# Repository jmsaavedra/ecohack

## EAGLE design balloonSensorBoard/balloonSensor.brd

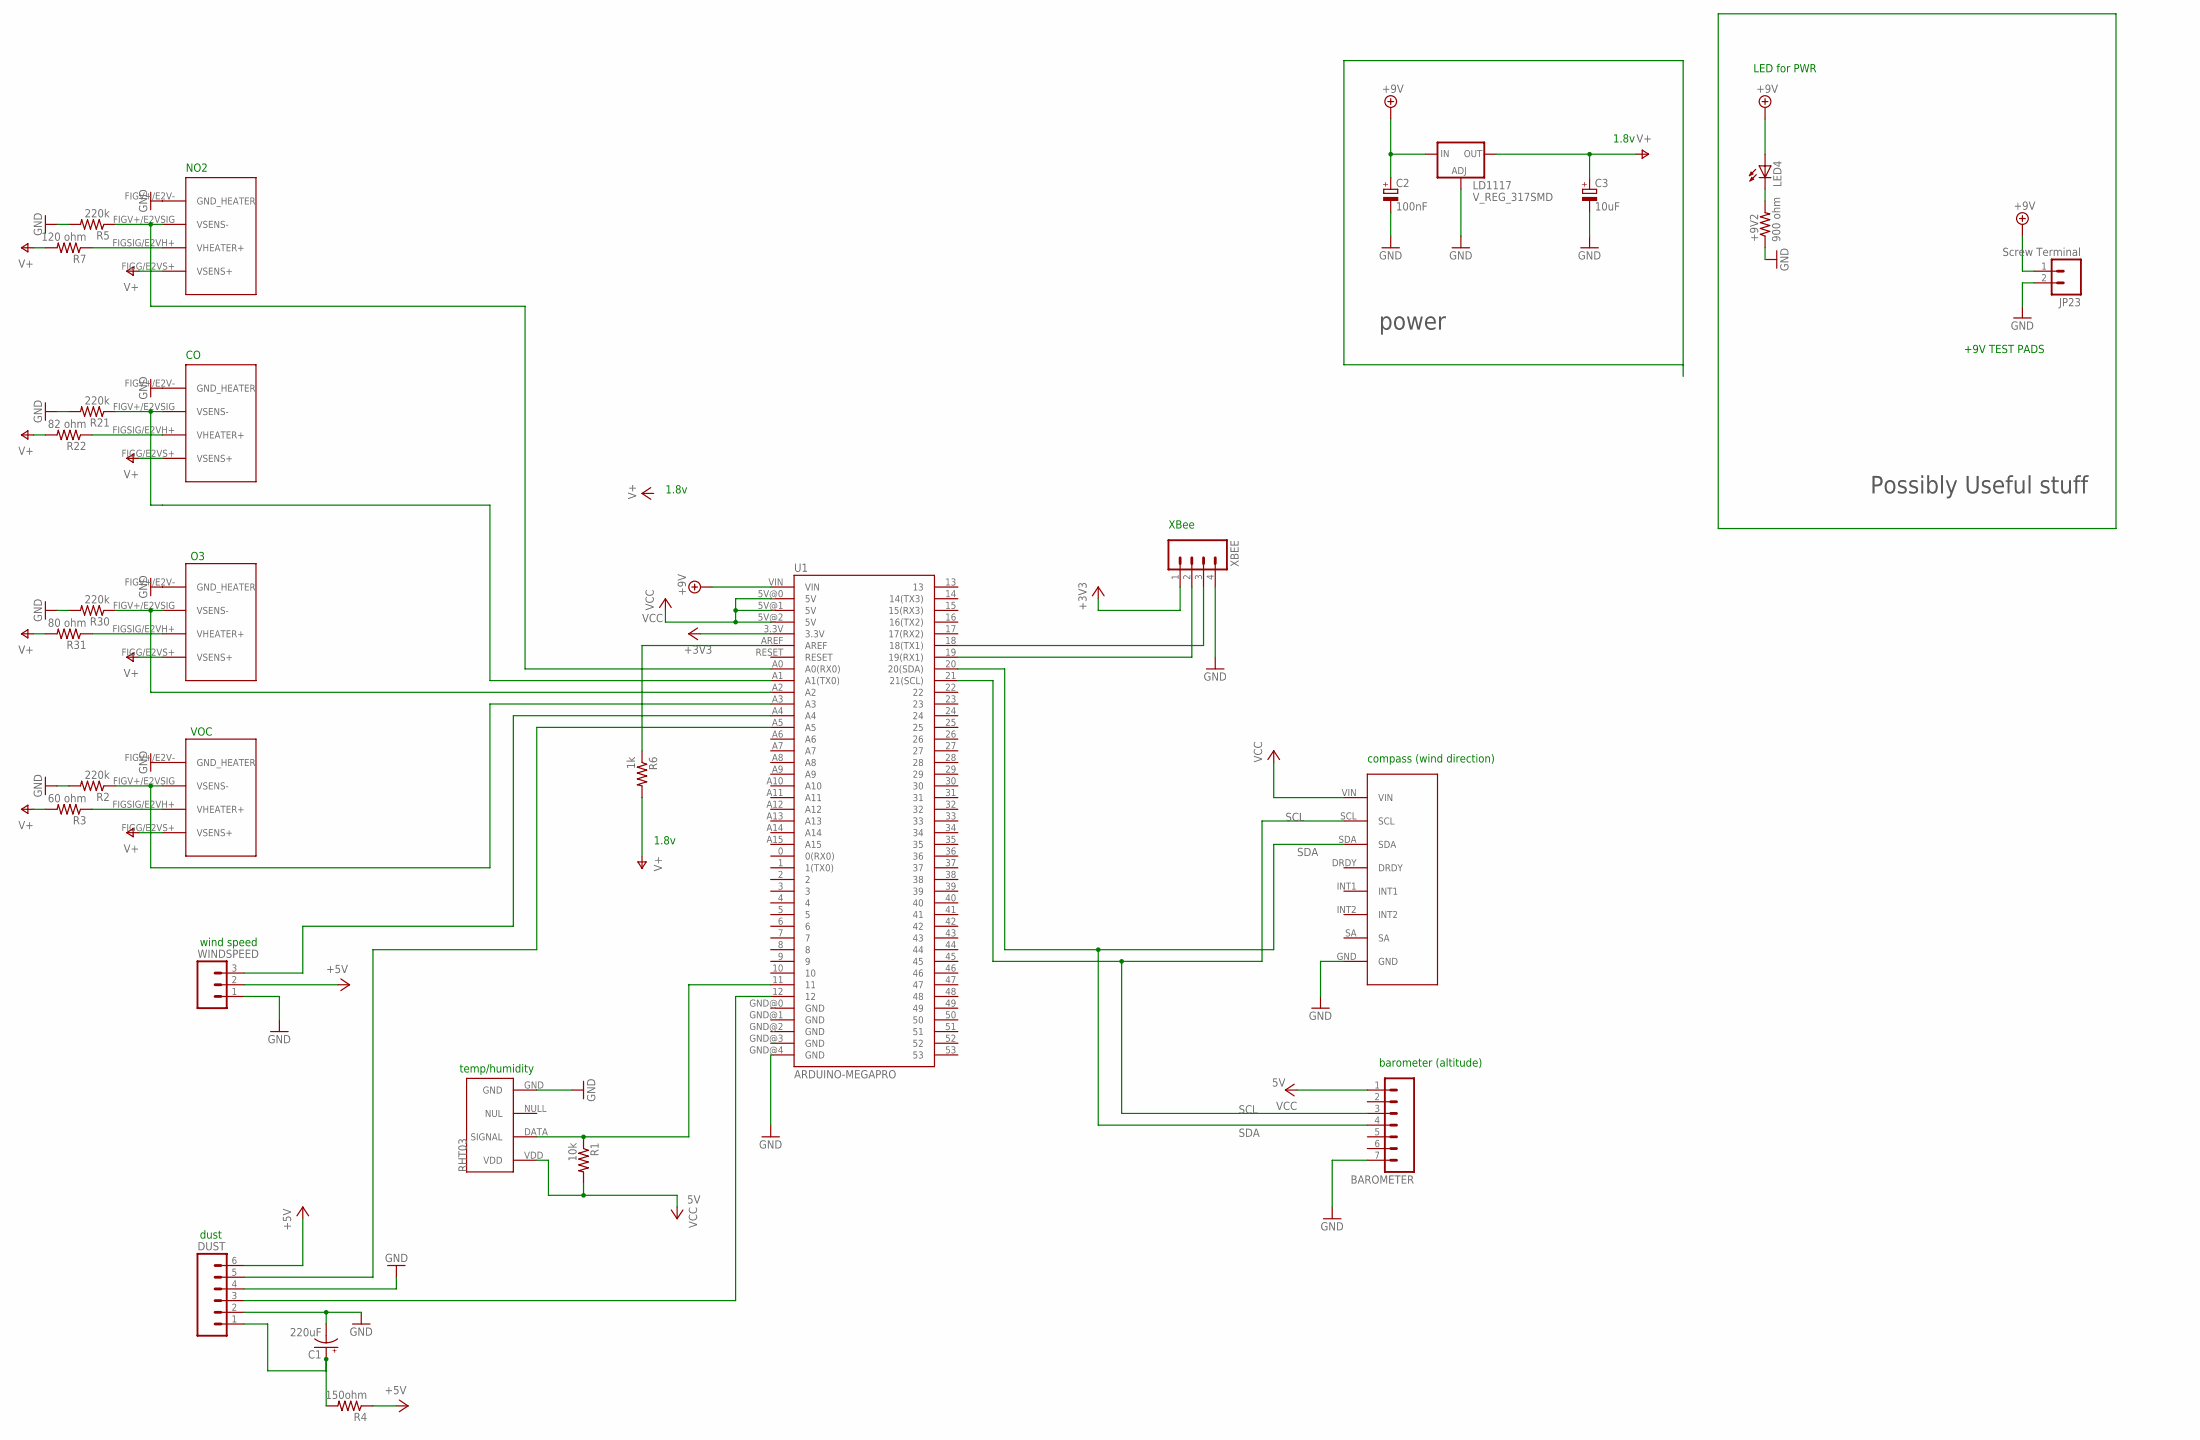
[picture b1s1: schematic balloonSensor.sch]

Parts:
+9V2: 900 ohm; R1206
BAROMETER: M07LONGPADS; 1X07_LONGPADS
C1: 220uF; EIA7343
C2: 100nF; CT3216
C3: 10uF; CT3216
CO: E2V; SR-4
COMPASS: COMPASS
DUST: M06LONGPADS; 1X06_LONGPADS
JP23: Screw Terminal; SCREWTERMINAL-5MM-2
LD1117: V_REG_317SMD; SOT223
LED4: LED3MM
NO2: E2V NO2; SR-4
O3: E2V Ozone; SR-4
R1: 10k; R1206
R2, R5, R21, R30: 220k; R1206
R3: 60 ohm; R1206
R4: 150ohm; R1206
R6: 1k; R1206
R7: 120 ohm; R1206
R22: 82 ohm; R1206
R31: 80 ohm; R1206
TEMP/HUMIDITY: RHT03; 1X04_LOCK
U1: ARDUINO-MEGAPRO; ARDUINO_MEGA-PRO-3.3V
VOC: E2V Ozone; SR-4
WINDSPEED: M03LONGPADS; 1X03_LONGPADS
XBEE: M04LONGPADS; 1X04_LONGPADS

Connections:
3: R1.1, TEMP/HUMIDITY.DATA (SIGNAL), U1.11
5V: R1.2, TEMP/HUMIDITY.VDD
+3V3: U1.3.3V, XBEE.1
+5V: DUST.6, R4.1, WINDSPEED.2
+9V: C2.+, JP23.1, LD1117.3 (IN), LED4.A, U1.VIN
GND: +9V2.1, BAROMETER.7, C1.C (-), C2.-, C3.-, CO.FIGV+/E2V- (GND_HEATER), COMPASS.GND, DUST.2, DUST.4, JP23.2, LD1117.1 (ADJ), NO2.FIGV+/E2V- (GND_HEATER), O3.FIGV+/E2V- (GND_HEATER), R2.2, R5.2, R21.2, R30.2, TEMP/HUMIDITY.GND, U1.GND@4 (GND), VOC.FIGV+/E2V- (GND_HEATER), WINDSPEED.1, XBEE.4
unnamed: R3.1, VOC.FIGSIG/E2VH+ (VHEATER+)
unnamed: R2.1, U1.A3, VOC.FIGV+/E2VSIG (VSENS-)
unnamed: R6.1, U1.AREF
unnamed: U1.19 (19(RX1)), XBEE.2
unnamed: U1.A4, WINDSPEED.3
unnamed: C1.A (+), DUST.1, R4.2
unnamed: DUST.3, U1.12
unnamed: DUST.5, U1.A5
unnamed: U1.18 (18(TX1)), XBEE.3
unnamed: +9V2.2, LED4.K (C)
unnamed: CO.FIGSIG/E2VH+ (VHEATER+), R22.1
unnamed: NO2.FIGSIG/E2VH+ (VHEATER+), R7.1
unnamed: O3.FIGSIG/E2VH+ (VHEATER+), R31.1
unnamed: CO.FIGV+/E2VSIG (VSENS-), R21.1, U1.A1 (A1(TX0))
unnamed: NO2.FIGV+/E2VSIG (VSENS-), R5.1, U1.A0 (A0(RX0))
unnamed: O3.FIGV+/E2VSIG (VSENS-), R30.1, U1.A2
SCL: BAROMETER.3, COMPASS.SCL, U1.21 (21(SCL))
SDA: BAROMETER.4, COMPASS.SDA, U1.20 (20(SDA))
V+: C3.+, CO.FIGG/E2VS+ (VSENS+), LD1117.2 (OUT), NO2.FIGG/E2VS+ (VSENS+), O3.FIGG/E2VS+ (VSENS+), R3.2, R6.2, R7.2, R22.2, R31.2, VOC.FIGG/E2VS+ (VSENS+)
VCC: BAROMETER.1, COMPASS.VIN, U1.5V@0 (5V), U1.5V@1 (5V), U1.5V@2 (5V)

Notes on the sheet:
LED for PWR
+9V TEST PADS
NO2
Possibly Useful stuff
power
VOC
wind speed
dust
compass (wind direction)
XBee
temp/humidity
1.8v
barometer (altitude)

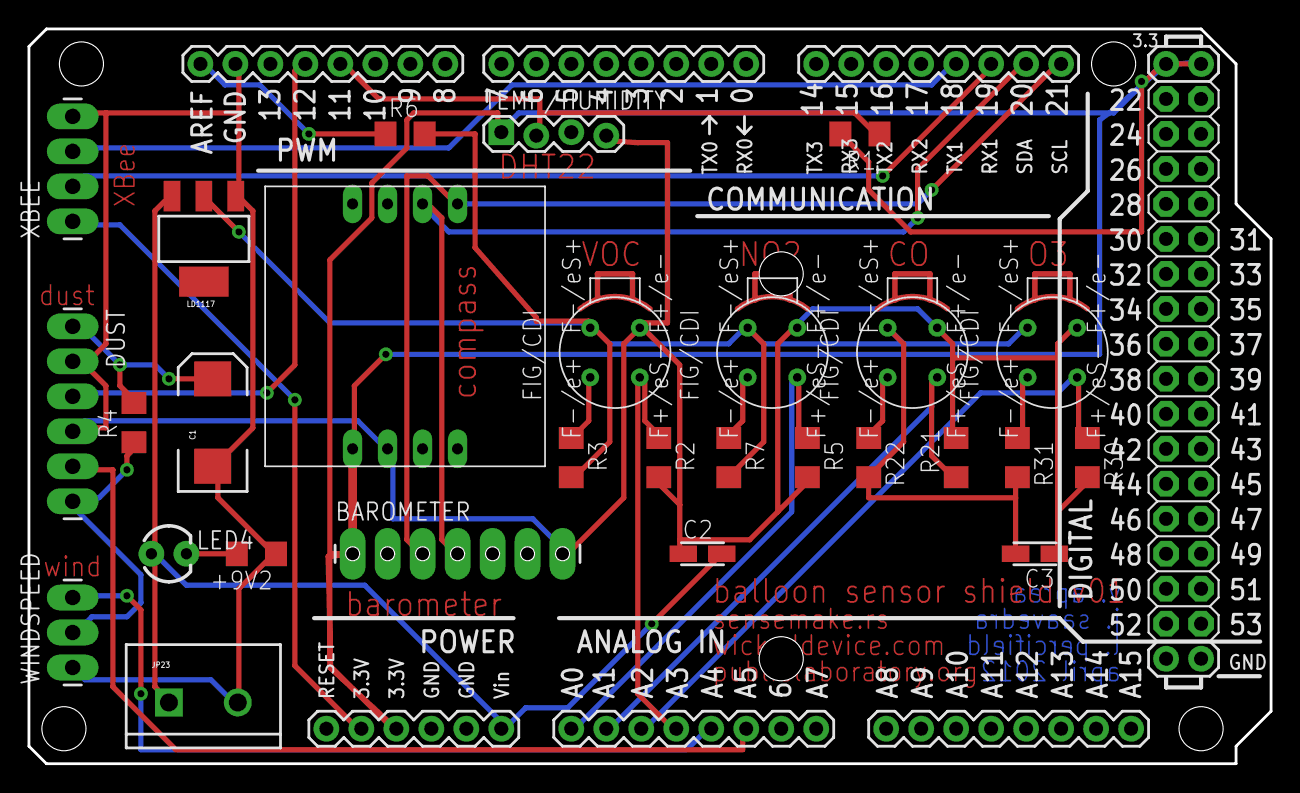
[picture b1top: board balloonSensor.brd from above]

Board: 2 copper layers, 90.2 x 53.3 mm, 29 parts (0 on the bottom side), 26 nets.

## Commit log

2012-04-15 updated .sch, .brd
2012-04-16 added sensors and miscellaneous parts and routed board
2012-04-16 added cap size, mod a couple vins
2012-04-16 added top copper text
2012-04-21 fixed shorted trace near compass pin 5
2012-04-21 updated resistors
2012-04-21 initial commit of integrated software, missing dust sensor
2012-04-22 organized, added dust
2012-04-22 added BMP
2012-04-22 revamped arduino code
2012-04-22 updated arduino

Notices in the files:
parts and their libraries:
SparkFun: Licensing: CC v3.0 Share-Alike You are welcome to use this library for commercial purposes.
